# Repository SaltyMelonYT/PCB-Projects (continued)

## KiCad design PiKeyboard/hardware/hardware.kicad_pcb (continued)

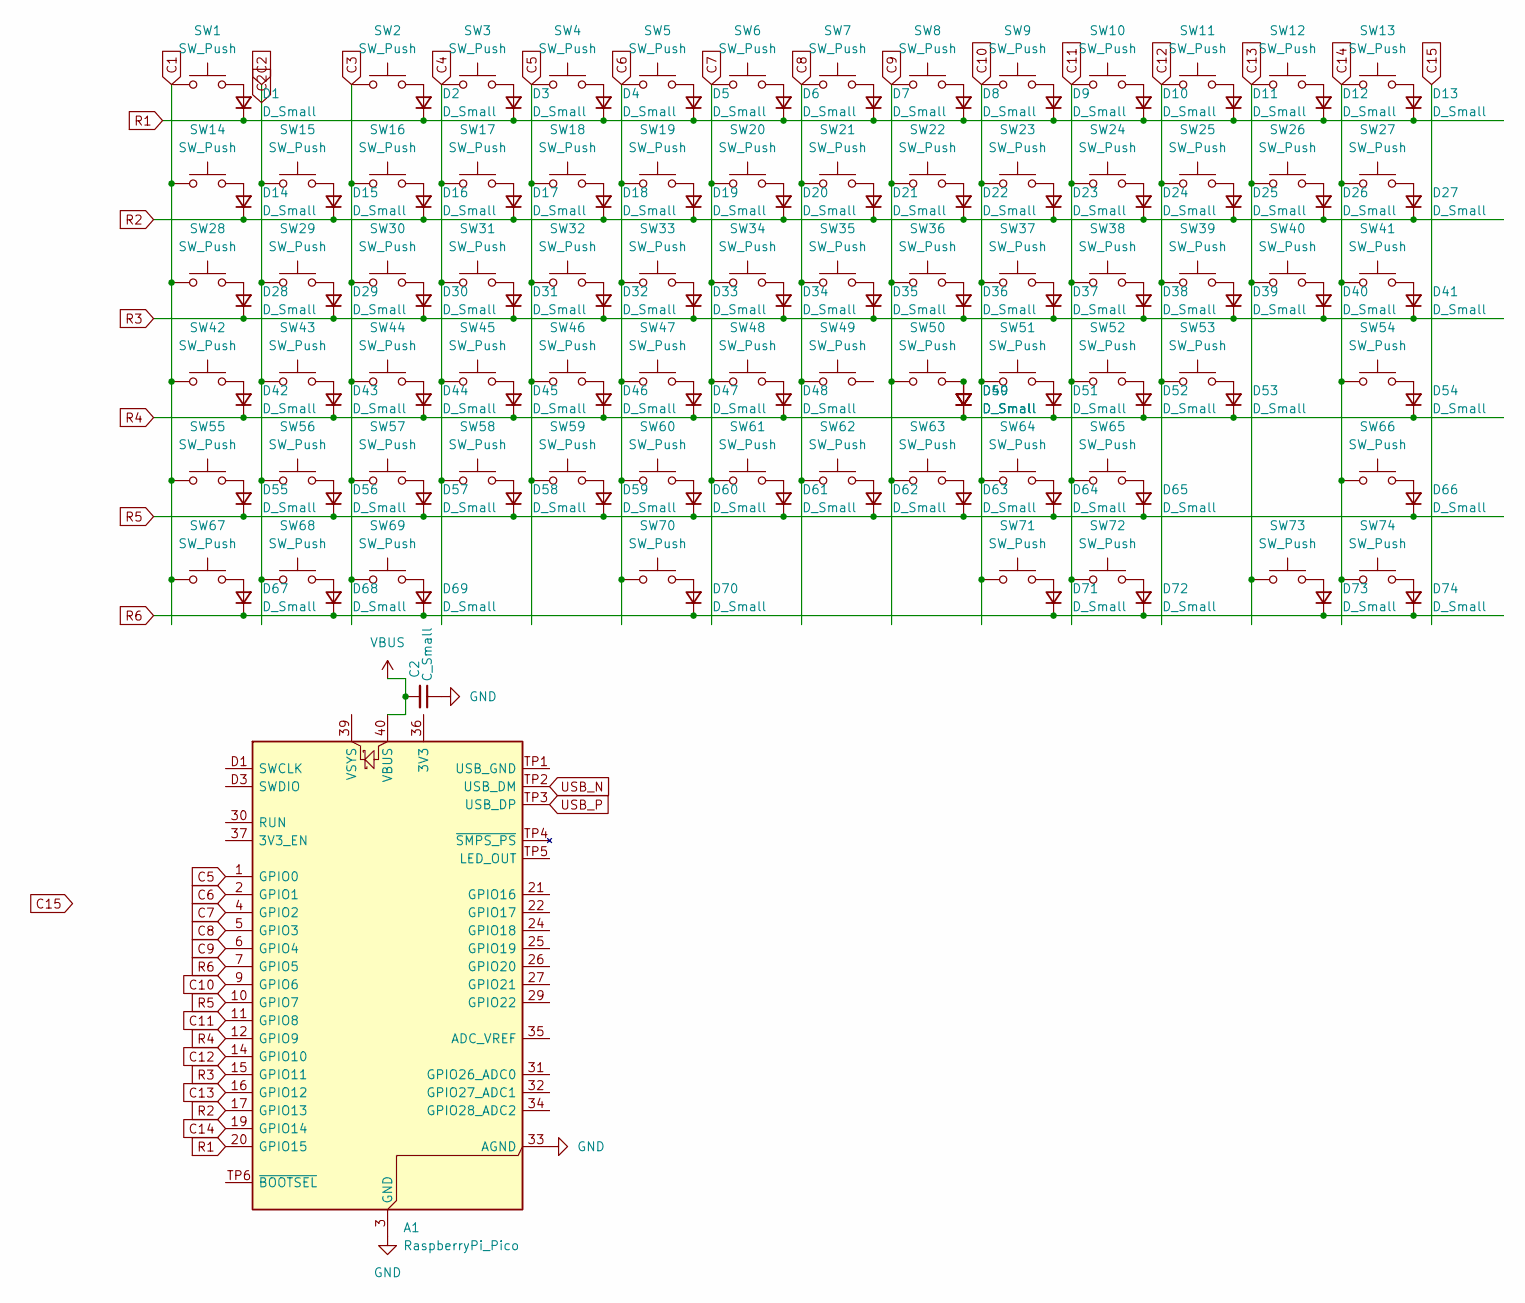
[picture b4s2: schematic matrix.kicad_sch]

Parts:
A1: RaspberryPi_Pico; RaspberryPi_Pico_SMD
C2: C_Small; C_0805_2012Metric_Pad1.18x1.45mm_HandSolder
D1, D2, D3, D4, D5, D6, D7, D8, D9, D10, D11, D12, D13, D14, D15, D16, D17, D18, D19, D20, D21, D22, D23, D24, D25, D26, D27, D28, D29, D30, D31, D32, D33, D34, D35, D36, D37, D38, D39, D40, D41, D42, D43, D44, D45, D46, D47, D48, D49, D50, D51, D52, D53, D54, D55, D56, D57, D58, D59, D60, D61, D62, D63, D64, D65, D66, D67, D68, D69, D70, D71, D72, D73, D74: D_Small; D_0402_1005Metric_Pad0.77x0.64mm_HandSolder
SW1, SW2, SW3, SW4, SW5, SW6, SW7, SW8, SW9, SW10, SW11, SW12, SW13, SW14, SW15, SW16, SW17, SW18, SW19, SW20, SW21, SW22, SW23, SW24, SW25, SW26, SW29, SW30, SW31, SW32, SW33, SW34, SW35, SW36, SW37, SW38, SW39, SW40, SW43, SW44, SW45, SW46, SW47, SW48, SW49, SW50, SW51, SW52, SW53, SW56, SW57, SW58, SW59, SW60, SW61, SW62, SW63, SW64, SW65: SW_Push; SW_Cherry_MX_PCB_1.00u
SW27, SW55: SW_Push; SW_Cherry_MX_PCB_2.00u
SW28, SW41: SW_Push; SW_Cherry_MX_PCB_1.50u
SW42: SW_Push; SW_Cherry_MX_PCB_1.75u
SW54: SW_Push; SW_Cherry_MX_PCB_2.25u
SW66: SW_Push; SW_Cherry_MX_PCB_3.00u
SW67, SW68, SW69, SW71, SW72, SW73, SW74: SW_Push; SW_Cherry_MX_PCB_1.25u
SW70: SW_Push; SW_Cherry_MX_PCB_6.25u

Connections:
C1: SW1.1, SW14.1, SW28.1, SW42.1, SW55.1, SW67.1
C2: SW15.1, SW29.1, SW43.1, SW56.1, SW68.1
C3: SW2.1, SW16.1, SW30.1, SW44.1, SW57.1, SW69.1
C4: SW3.1, SW17.1, SW31.1, SW45.1, SW58.1
C5: A1.1 (GPIO0), SW4.1, SW18.1, SW32.1, SW46.1, SW59.1
C6: A1.2 (GPIO1), SW5.1, SW19.1, SW33.1, SW47.1, SW60.1, SW70.1
C7: A1.4 (GPIO2), SW6.1, SW20.1, SW34.1, SW48.1, SW61.1
C8: A1.5 (GPIO3), SW7.1, SW21.1, SW35.1, SW49.1, SW62.1
C9: A1.6 (GPIO4), SW8.1, SW22.1, SW36.1, SW50.1, SW63.1
C10: A1.9 (GPIO6), SW9.1, SW23.1, SW37.1, SW51.1, SW64.1, SW71.1
C11: A1.11 (GPIO8), SW10.1, SW24.1, SW38.1, SW52.1, SW65.1, SW72.1
C12: A1.14 (GPIO10), SW11.1, SW25.1, SW39.1, SW53.1
C13: A1.16 (GPIO12), SW12.1, SW26.1, SW40.1, SW73.1
C14: A1.19 (GPIO14), SW13.1, SW27.1, SW41.1, SW54.1, SW66.1, SW74.1
GND: A1.3 (GND), A1.8 (GND), A1.13 (GND), A1.18 (GND), A1.23 (GND), A1.28 (GND), A1.33 (AGND), A1.38 (GND), A1.D2 (GND), C2.1; also elsewhere on the board
unnamed: D1.2 (A), SW1.2
unnamed: D2.2 (A), SW2.2
unnamed: D3.2 (A), SW3.2
unnamed: D4.2 (A), SW4.2
unnamed: D5.2 (A), SW5.2
unnamed: D6.2 (A), SW6.2
unnamed: D7.2 (A), SW7.2
unnamed: D8.2 (A), SW8.2
unnamed: D9.2 (A), SW9.2
unnamed: D10.2 (A), SW10.2
unnamed: D11.2 (A), SW11.2
unnamed: D12.2 (A), SW12.2
unnamed: D13.2 (A), SW13.2
unnamed: D14.2 (A), SW14.2
unnamed: D15.2 (A), SW15.2
unnamed: D16.2 (A), SW16.2
unnamed: D17.2 (A), SW17.2
unnamed: D18.2 (A), SW18.2
unnamed: D19.2 (A), SW19.2
unnamed: D20.2 (A), SW20.2
unnamed: D21.2 (A), SW21.2
unnamed: D22.2 (A), SW22.2
unnamed: D23.2 (A), SW23.2
unnamed: D24.2 (A), SW24.2
unnamed: D25.2 (A), SW25.2
unnamed: D26.2 (A), SW26.2
unnamed: D27.2 (A), SW27.2
unnamed: D28.2 (A), SW28.2
unnamed: D29.2 (A), SW29.2
unnamed: D30.2 (A), SW30.2
unnamed: D31.2 (A), SW31.2
unnamed: D32.2 (A), SW32.2
unnamed: D33.2 (A), SW33.2
unnamed: D34.2 (A), SW34.2
unnamed: D35.2 (A), SW35.2
unnamed: D36.2 (A), SW36.2
unnamed: D37.2 (A), SW37.2
unnamed: D38.2 (A), SW38.2
unnamed: D39.2 (A), SW39.2
unnamed: D40.2 (A), SW40.2
unnamed: D41.2 (A), SW41.2
unnamed: D42.2 (A), SW42.2
unnamed: D43.2 (A), SW43.2
unnamed: D44.2 (A), SW44.2
unnamed: D45.2 (A), SW45.2
unnamed: D46.2 (A), SW46.2
unnamed: D47.2 (A), SW47.2
unnamed: D48.2 (A), SW48.2
unnamed: D49.2 (A), D50.2 (A), SW50.2
unnamed: D51.2 (A), SW51.2
unnamed: D52.2 (A), SW52.2
unnamed: D53.2 (A), SW53.2
unnamed: D54.2 (A), SW54.2
unnamed: D55.2 (A), SW55.2
unnamed: D56.2 (A), SW56.2
unnamed: D57.2 (A), SW57.2
unnamed: D58.2 (A), SW58.2
unnamed: D59.2 (A), SW59.2
unnamed: D60.2 (A), SW60.2
unnamed: D61.2 (A), SW61.2
unnamed: D62.2 (A), SW62.2
unnamed: D63.2 (A), SW63.2
unnamed: D64.2 (A), SW64.2
unnamed: D65.2 (A), SW65.2
unnamed: D66.2 (A), SW66.2
unnamed: D67.2 (A), SW67.2
unnamed: D68.2 (A), SW68.2
unnamed: D69.2 (A), SW69.2
unnamed: D70.2 (A), SW70.2
unnamed: D71.2 (A), SW71.2
unnamed: D72.2 (A), SW72.2
unnamed: D73.2 (A), SW73.2
unnamed: D74.2 (A), SW74.2
R1: A1.20 (GPIO15), D1.1 (K), D2.1 (K), D3.1 (K), D4.1 (K), D5.1 (K), D6.1 (K), D7.1 (K), D8.1 (K), D9.1 (K), D10.1 (K), D11.1 (K), D12.1 (K), D13.1 (K)
R2: A1.17 (GPIO13), D14.1 (K), D15.1 (K), D16.1 (K), D17.1 (K), D18.1 (K), D19.1 (K), D20.1 (K), D21.1 (K), D22.1 (K), D23.1 (K), D24.1 (K), D25.1 (K), D26.1 (K), D27.1 (K)
R3: A1.15 (GPIO11), D28.1 (K), D29.1 (K), D30.1 (K), D31.1 (K), D32.1 (K), D33.1 (K), D34.1 (K), D35.1 (K), D36.1 (K), D37.1 (K), D38.1 (K), D39.1 (K), D40.1 (K), D41.1 (K)
R4: A1.12 (GPIO9), D42.1 (K), D43.1 (K), D44.1 (K), D45.1 (K), D46.1 (K), D47.1 (K), D48.1 (K), D49.1 (K), D50.1 (K), D51.1 (K), D52.1 (K), D53.1 (K), D54.1 (K)
R5: A1.10 (GPIO7), D55.1 (K), D56.1 (K), D57.1 (K), D58.1 (K), D59.1 (K), D60.1 (K), D61.1 (K), D62.1 (K), D63.1 (K), D64.1 (K), D65.1 (K), D66.1 (K)
R6: A1.7 (GPIO5), D67.1 (K), D68.1 (K), D69.1 (K), D70.1 (K), D71.1 (K), D72.1 (K), D73.1 (K), D74.1 (K)
USB_N: A1.TP2 (USB_DM); also elsewhere on the board
USB_P: A1.TP3 (USB_DP); also elsewhere on the board
VBUS: A1.40 (VBUS), C2.2; also elsewhere on the board

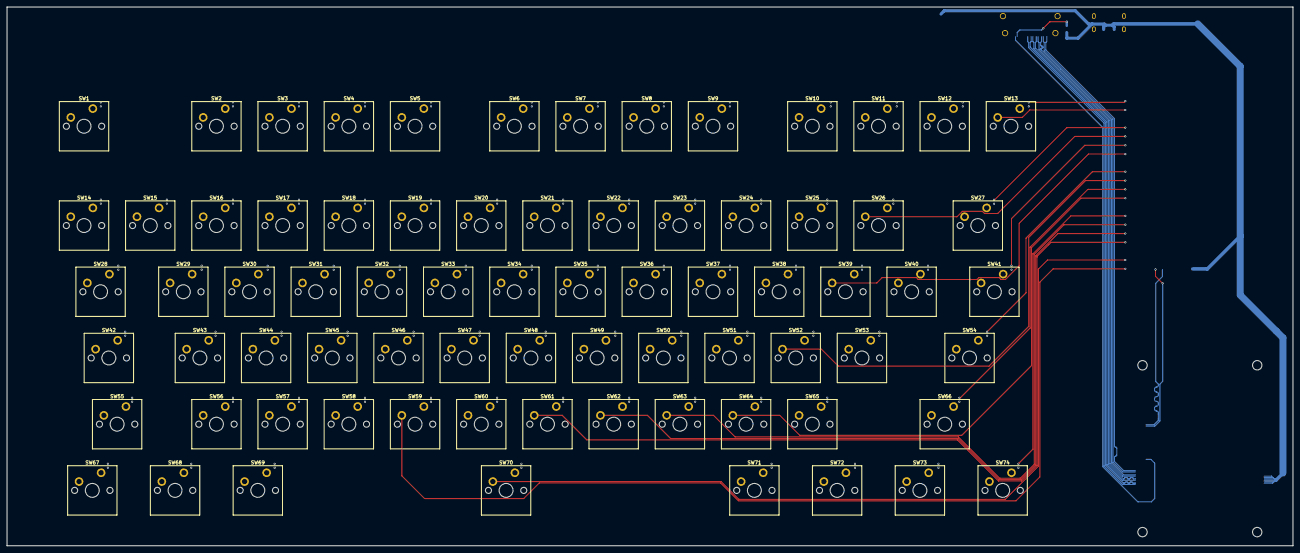
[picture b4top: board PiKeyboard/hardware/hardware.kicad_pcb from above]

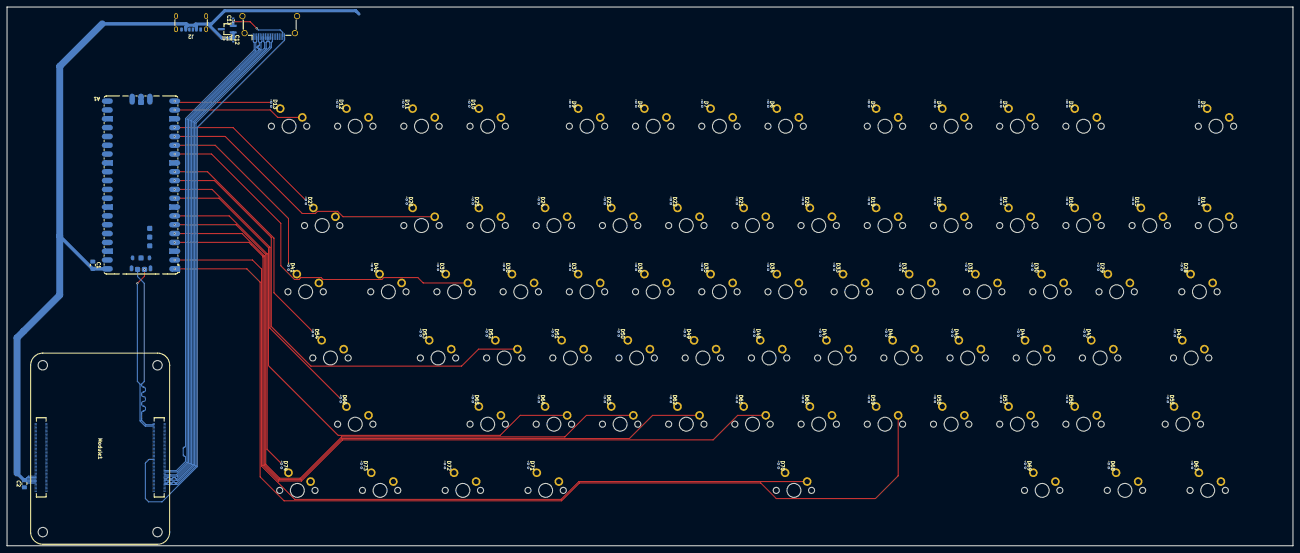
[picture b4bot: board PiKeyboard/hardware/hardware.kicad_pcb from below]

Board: 4 copper layers, 370.0 x 155.0 mm, 157 parts (83 on the bottom side), 109 nets.

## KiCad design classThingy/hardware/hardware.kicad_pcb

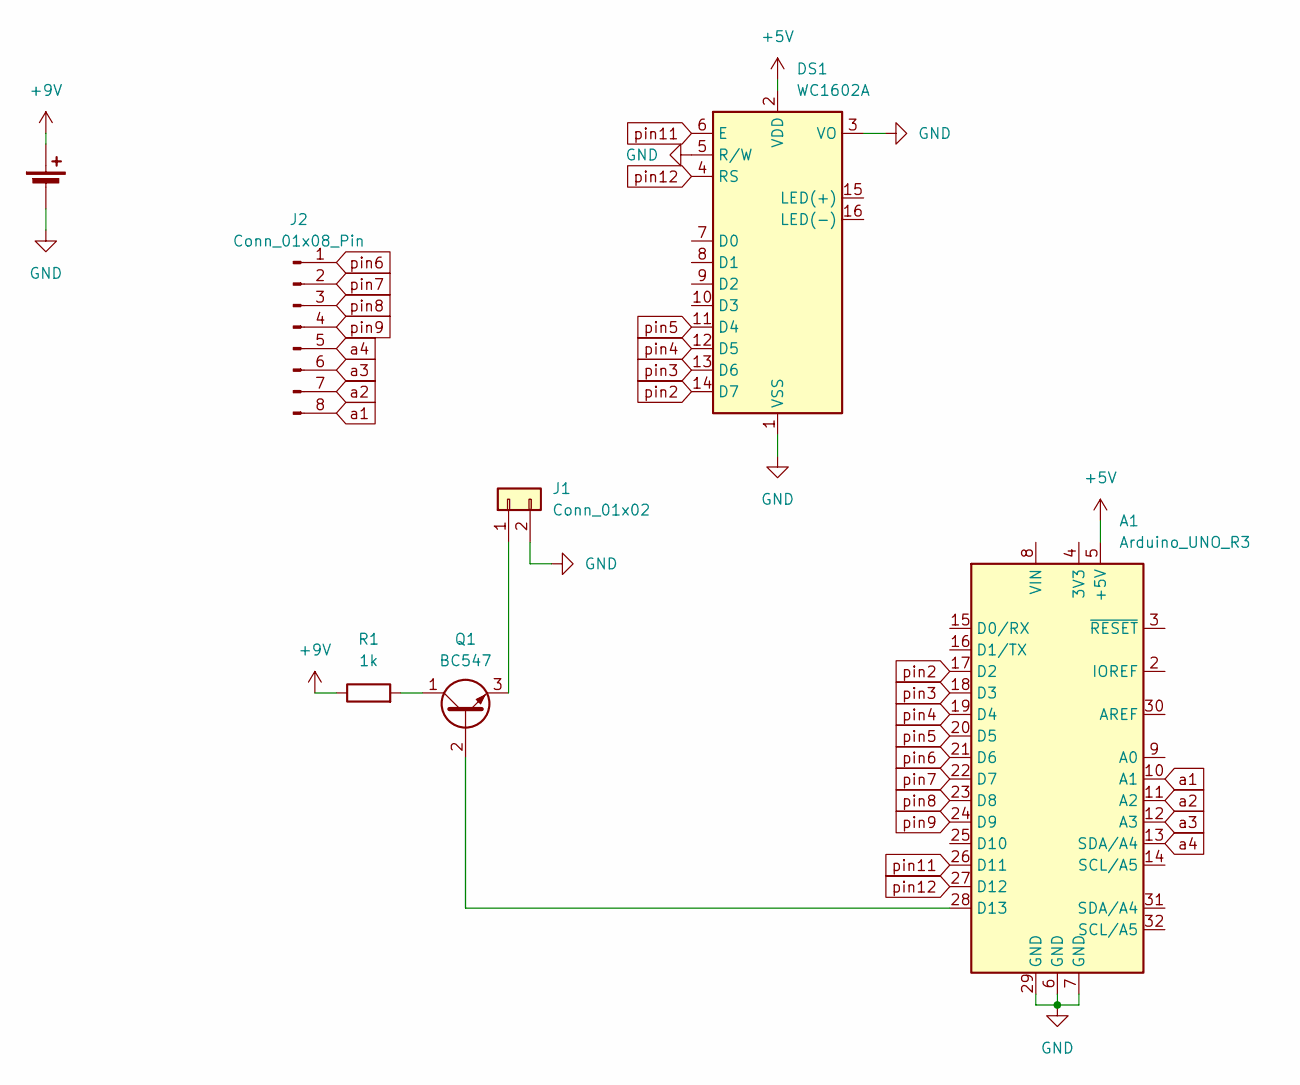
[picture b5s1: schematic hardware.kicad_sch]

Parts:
A1: Arduino_UNO_R3
BT1: +9V; BatteryHolder_Eagle_12BH611-GR
DS1: WC1602A
J1: Conn_01x02; PinHeader_1x02_P1.27mm_Vertical
J2: Conn_01x08_Pin; PinHeader_1x08_P1.27mm_Vertical
Q1: BC547; TO-92_Inline
R1: 1k; R_2512_6332Metric_Pad1.40x3.35mm_HandSolder

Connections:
+5V: A1.5 (+5V), DS1.2 (VDD)
+9V: BT1.1 (+), R1.1
GND: A1.6 (GND), A1.7 (GND), A1.29 (GND), BT1.2 (-), DS1.1 (VSS), DS1.3 (VO), DS1.5 (R/W), J1.2
unnamed: A1.28 (D13), Q1.2 (B)
unnamed: J1.1, Q1.3 (E)
unnamed: Q1.1 (C), R1.2
a1: A1.10 (A1), J2.8
a2: A1.11 (A2), J2.7
a3: A1.12 (A3), J2.6
a4: A1.13 (SDA/A4), J2.5
pin2: A1.17 (D2), DS1.14 (D7)
pin3: A1.18 (D3), DS1.13 (D6)
pin4: A1.19 (D4), DS1.12 (D5)
pin5: A1.20 (D5), DS1.11 (D4)
pin6: A1.21 (D6), J2.1
pin7: A1.22 (D7), J2.2
pin8: A1.23 (D8), J2.3
pin9: A1.24 (D9), J2.4
pin11: A1.26 (D11), DS1.6 (E)
pin12: A1.27 (D12), DS1.4 (RS)

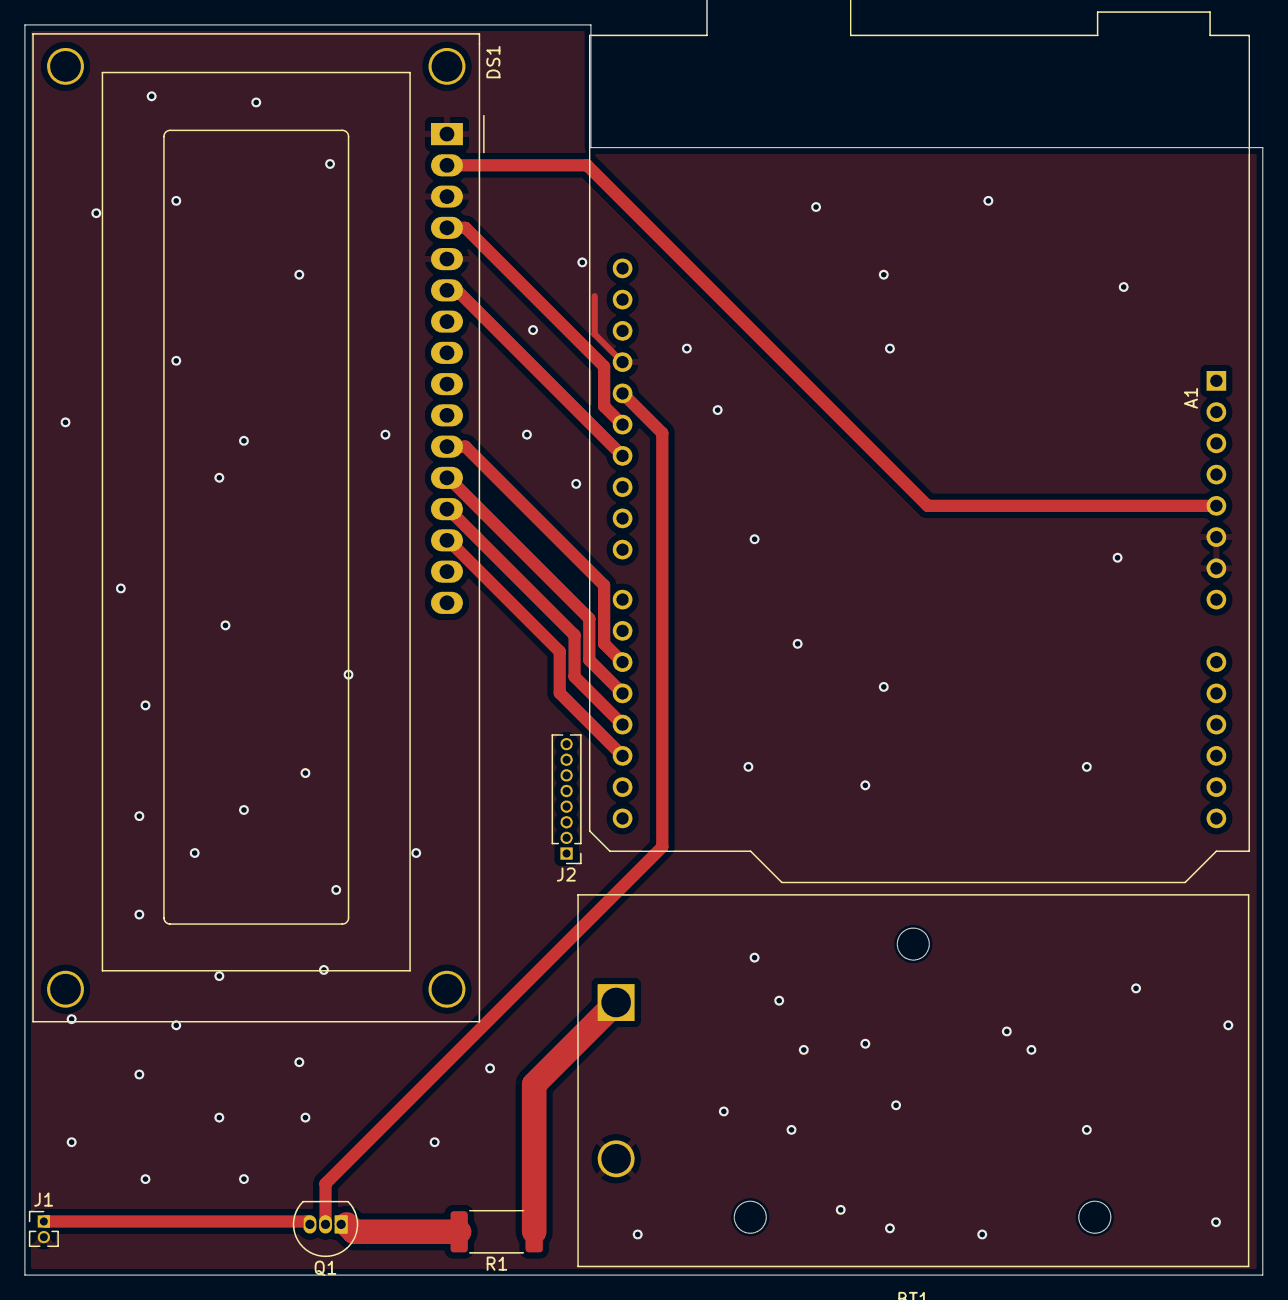
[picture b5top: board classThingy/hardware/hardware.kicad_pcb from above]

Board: 4 copper layers, 100.6 x 101.6 mm, 7 parts (0 on the bottom side), 20 nets.

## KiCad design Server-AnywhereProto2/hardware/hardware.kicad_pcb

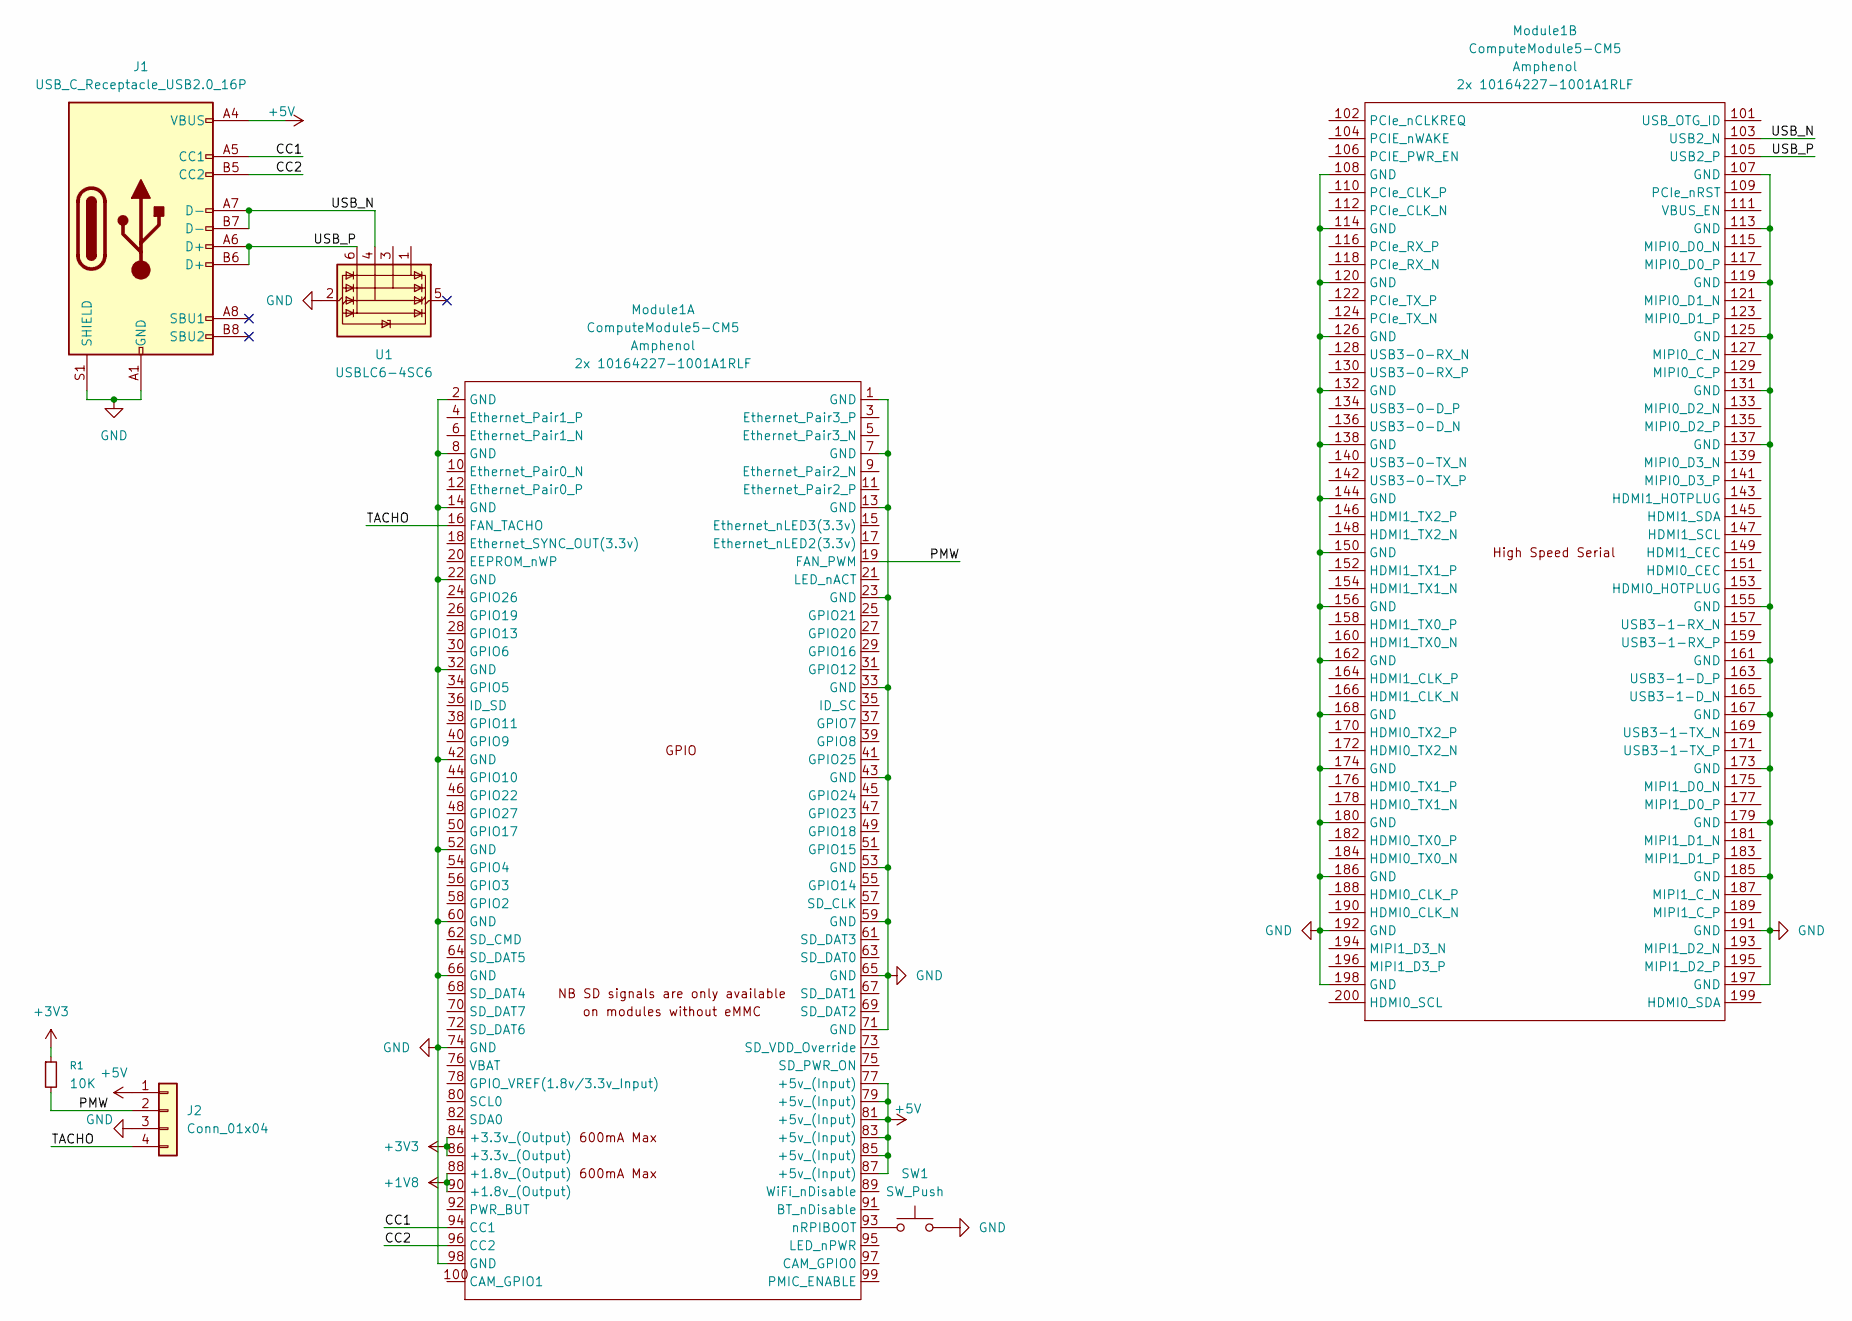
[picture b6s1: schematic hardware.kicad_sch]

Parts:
J1: USB_C_Receptacle_USB2.0_16P; USB_C_Receptacle_GCT_USB4105-xx-A_16P_TopMnt_Horizontal
J2: Conn_01x04; JST_SH_BM04B-SRSS-TB_1x04-1MP_P1.00mm_Vertical
Module1: ComputeModule5-CM5; Raspberry-Pi-5-Compute-Module
R1: 10K; R_2512_6332Metric_Pad1.40x3.35mm_HandSolder
SW1: SW_Push; SW_PUSH_6mm
U1: USBLC6-4SC6; SOT-23-6

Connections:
+1V8: Module1.88 (+1.8v_(Output)), Module1.90 (+1.8v_(Output))
+3V3: Module1.84 (+3.3v_(Output)), Module1.86 (+3.3v_(Output)), R1.1
+5V: J1.A4 (VBUS), J1.A9 (VBUS), J1.B4 (VBUS), J1.B9 (VBUS), J2.1, Module1.77 (+5v_(Input)), Module1.79 (+5v_(Input)), Module1.81 (+5v_(Input)), Module1.83 (+5v_(Input)), Module1.85 (+5v_(Input)), Module1.87 (+5v_(Input))
/CC1: J1.A5 (CC1), Module1.94 (CC1)
/CC2: J1.B5 (CC2), Module1.96 (CC2)
/PMW: J2.2, Module1.19 (FAN_PWM), R1.2
/TACHO: J2.4, Module1.16 (FAN_TACHO)
/USB_N: J1.A7 (D-), J1.B7 (D-), Module1.103 (USB2_N), U1.4 (I/O3)
/USB_P: J1.A6 (D+), J1.B6 (D+), Module1.105 (USB2_P), U1.6 (I/O4)
GND: J1.A1 (GND), J1.A12 (GND), J1.B1 (GND), J1.B12 (GND), J1.S1 (SHIELD), J2.3, Module1.1 (GND), Module1.2 (GND), Module1.7 (GND), Module1.8 (GND), Module1.13 (GND), Module1.14 (GND), Module1.22 (GND), Module1.23 (GND), Module1.32 (GND), Module1.33 (GND), Module1.42 (GND), Module1.43 (GND), Module1.52 (GND), Module1.53 (GND), Module1.59 (GND), Module1.60 (GND), Module1.65 (GND), Module1.66 (GND), Module1.71 (GND), Module1.74 (GND), Module1.98 (GND), Module1.107 (GND), Module1.108 (GND), Module1.113 (GND), Module1.114 (GND), Module1.119 (GND), Module1.120 (GND), Module1.125 (GND), Module1.126 (GND), Module1.131 (GND), Module1.132 (GND), Module1.137 (GND), Module1.138 (GND), Module1.144 (GND), Module1.150 (GND), Module1.155 (GND), Module1.156 (GND), Module1.161 (GND), Module1.162 (GND), Module1.167 (GND), Module1.168 (GND), Module1.173 (GND), Module1.174 (GND), Module1.179 (GND), Module1.180 (GND), Module1.185 (GND), Module1.186 (GND), Module1.191 (GND), Module1.192 (GND), Module1.197 (GND), Module1.198 (GND), SW1.2, U1.2 (GND)
unnamed: Module1.93 (nRPIBOOT), SW1.1

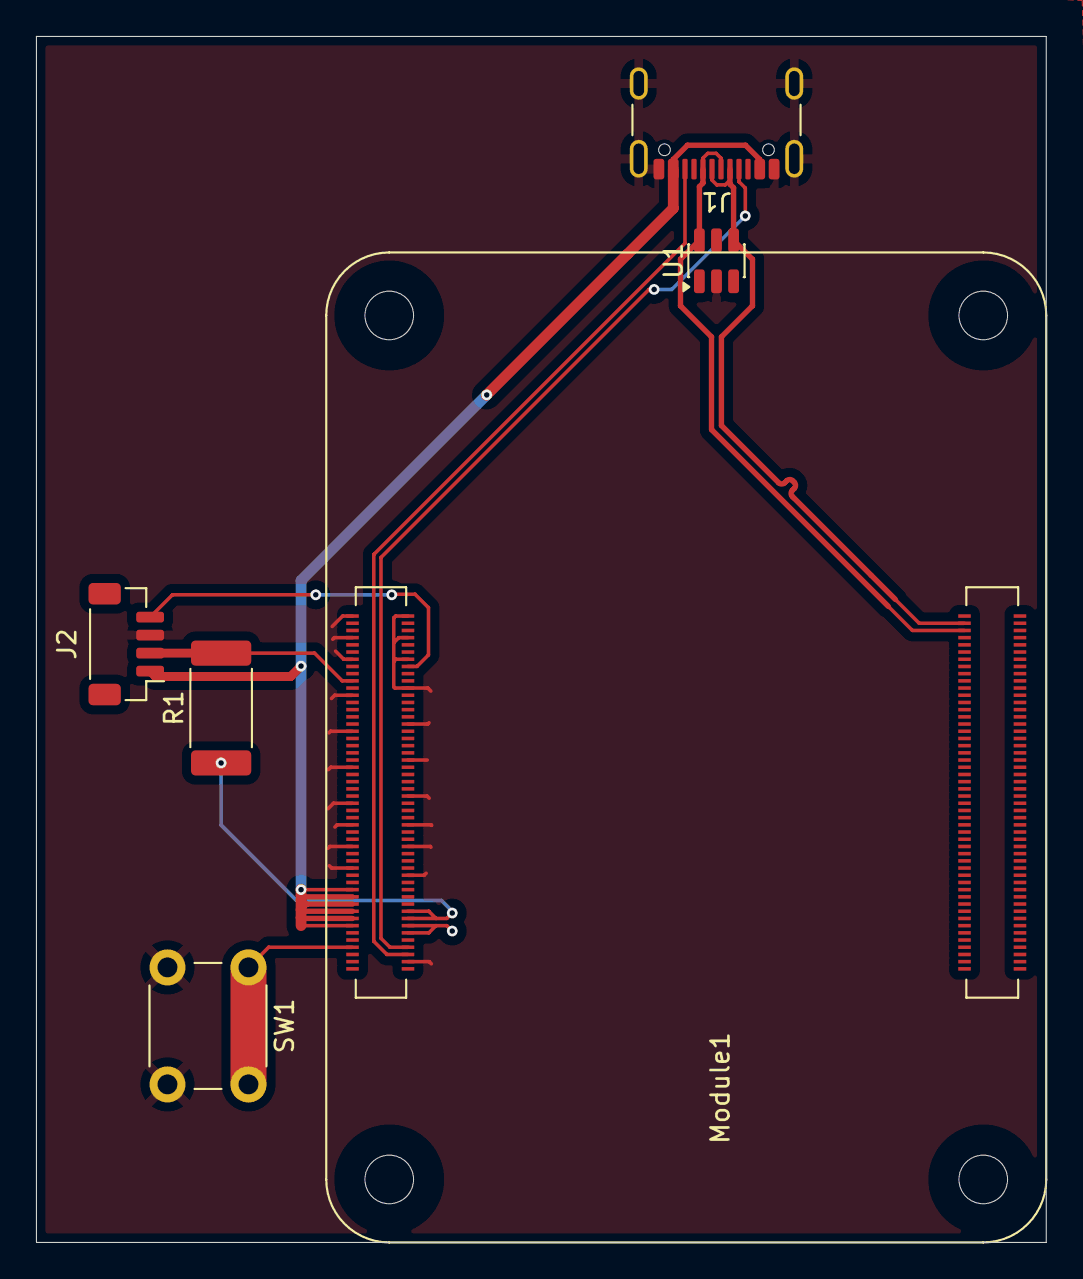
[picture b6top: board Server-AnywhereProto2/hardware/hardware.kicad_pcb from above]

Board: 2 copper layers, 56.1 x 67.0 mm, 6 parts (0 on the bottom side), 11 nets.

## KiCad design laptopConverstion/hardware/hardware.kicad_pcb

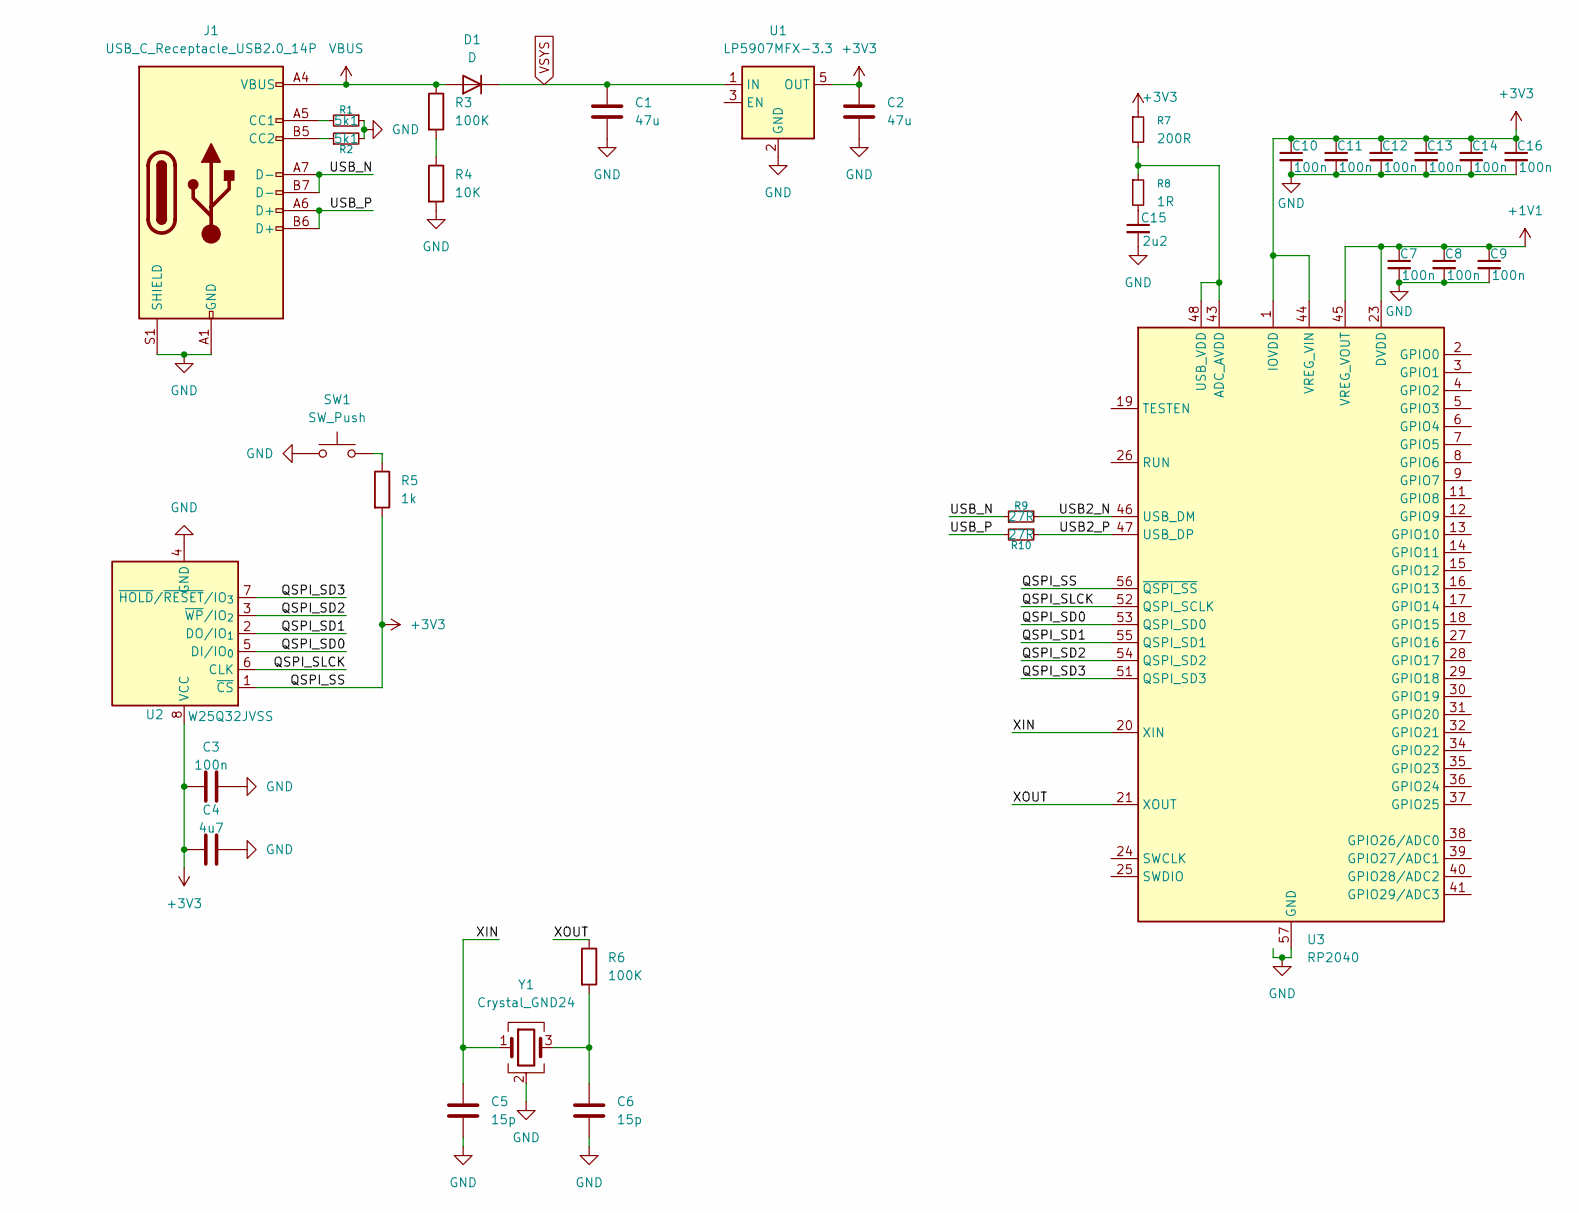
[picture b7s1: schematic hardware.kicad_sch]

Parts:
C1, C2: 47u; C_1812_4532Metric_Pad1.57x3.40mm_HandSolder
C3: 100n; C_1812_4532Metric_Pad1.57x3.40mm_HandSolder
C4: 4u7; C_1812_4532Metric_Pad1.57x3.40mm_HandSolder
C5, C6: 15p; C_1812_4532Metric_Pad1.57x3.40mm_HandSolder
C7, C8, C9, C10, C11, C12, C13, C14, C16: 100n; C_1206_3216Metric_Pad1.33x1.80mm_HandSolder
C15: 2u2; C_1206_3216Metric_Pad1.33x1.80mm_HandSolder
D1: D; D_1210_3225Metric_Pad1.42x2.65mm_HandSolder
J1: USB_C_Receptacle_USB2.0_14P; USB_C_Receptacle_GCT_USB4105-xx-A_16P_TopMnt_Horizontal
R1, R2: 5k1; R_1210_3225Metric_Pad1.30x2.65mm_HandSolder
R3: 100K; R_1210_3225Metric_Pad1.30x2.65mm_HandSolder
R4: 10K; R_1210_3225Metric_Pad1.30x2.65mm_HandSolder
R5: 1k; R_1210_3225Metric_Pad1.30x2.65mm_HandSolder
R6: 100K; R_0805_2012Metric_Pad1.20x1.40mm_HandSolder
R7: 200R; R_0805_2012Metric_Pad1.20x1.40mm_HandSolder
R8: 1R; R_0805_2012Metric_Pad1.20x1.40mm_HandSolder
R9, R10: 27R; R_0805_2012Metric_Pad1.20x1.40mm_HandSolder
SW1: SW_Push; SW_PUSH_6mm
U1: LP5907MFX-3.3; SOT-23-5
U2: W25Q32JVSS; SOIC-8_5.3x5.3mm_P1.27mm
U3: RP2040; QFN-56-1EP_7x7mm_P0.4mm_EP3.2x3.2mm
Y1: Crystal_GND24; Crystal_SMD_0603-4Pin_6.0x3.5mm_HandSoldering

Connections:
+1V1: C7.1, C8.1, C9.1, U3.23 (DVDD), U3.45 (VREG_VOUT), U3.50 (DVDD)
+3V3: C2.1, C3.1, C4.1, C10.1, C11.1, C12.1, C13.1, C14.1, C16.1, R5.2, R7.1, U1.5 (OUT), U2.1 (~CS), U2.8 (VCC), U3.1 (IOVDD), U3.10 (IOVDD), U3.22 (IOVDD), U3.33 (IOVDD), U3.42 (IOVDD), U3.44 (VREG_VIN), U3.49 (IOVDD), U3.56 (~QSPI_SS)
/QSPI_SD0: U2.5 (DI/IO_{0}), U3.53 (QSPI_SD0)
/QSPI_SD1: U2.2 (DO/IO_{1}), U3.55 (QSPI_SD1)
/QSPI_SD2: U2.3 (~WP/IO_{2}), U3.54 (QSPI_SD2)
/QSPI_SD3: U2.7 (~HOLD/~RESET/IO_{3}), U3.51 (QSPI_SD3)
/QSPI_SLCK: U2.6 (CLK), U3.52 (QSPI_SCLK)
/USB2_N: R9.2, U3.46 (USB_DM)
/USB2_P: R10.1, U3.47 (USB_DP)
/USB_N: J1.A7 (D-), J1.B7 (D-), R9.1
/USB_P: J1.A6 (D+), J1.B6 (D+), R10.2
/XIN: C5.1, U3.20 (XIN), Y1.1
/XOUT: R6.1, U3.21 (XOUT)
GND: C1.2, C2.2, C3.2, C4.2, C5.2, C6.2, C7.2, C8.2, C9.2, C10.2, C11.2, C12.2, C13.2, C14.2, C15.2, C16.2, J1.A1 (GND), J1.A12 (GND), J1.B1 (GND), J1.B12 (GND), J1.S1 (SHIELD), R1.1, R2.2, R4.2, SW1.1, U1.2 (GND), U2.4 (GND), U3.57 (GND), Y1.2 (G), Y1.4 (G)
unnamed: C6.1, R6.2, Y1.3
unnamed: C15.1, R8.2
unnamed: J1.A5 (CC1), R1.2
unnamed: J1.B5 (CC2), R2.1
unnamed: R3.2, R4.1
unnamed: R5.1, SW1.2
unnamed: R7.2, R8.1, U3.43 (ADC_AVDD), U3.48 (USB_VDD)
VBUS: D1.2 (A), J1.A4 (VBUS), J1.A9 (VBUS), J1.B4 (VBUS), J1.B9 (VBUS), R3.1
VSYS: C1.1, D1.1 (K), U1.1 (IN)

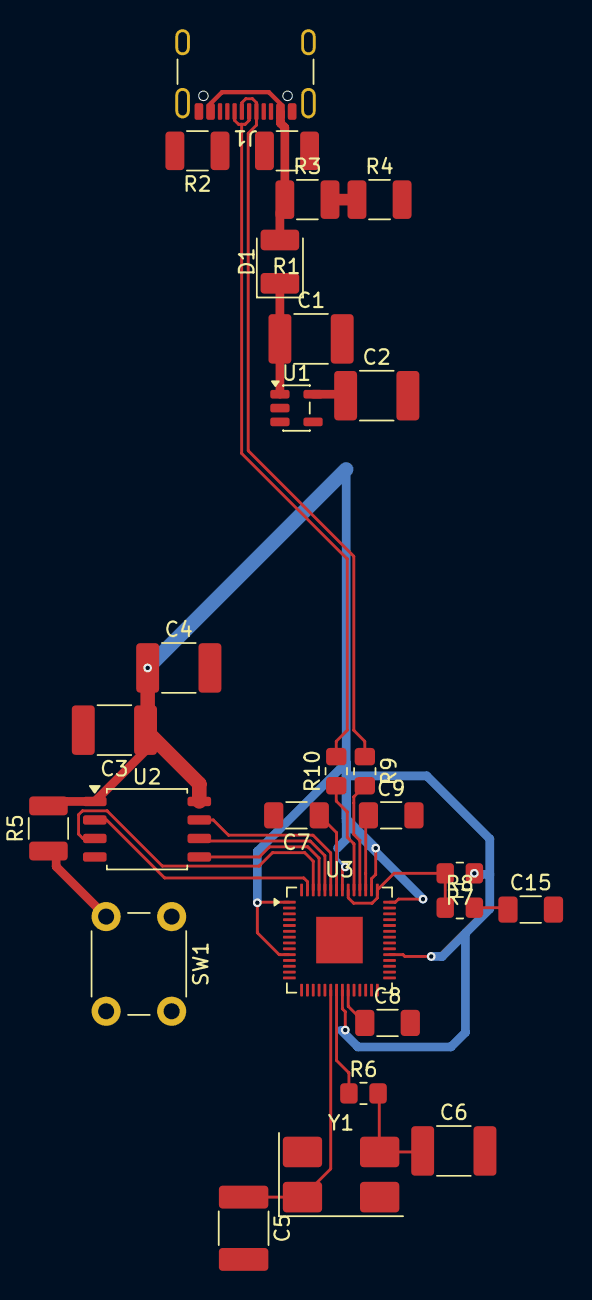
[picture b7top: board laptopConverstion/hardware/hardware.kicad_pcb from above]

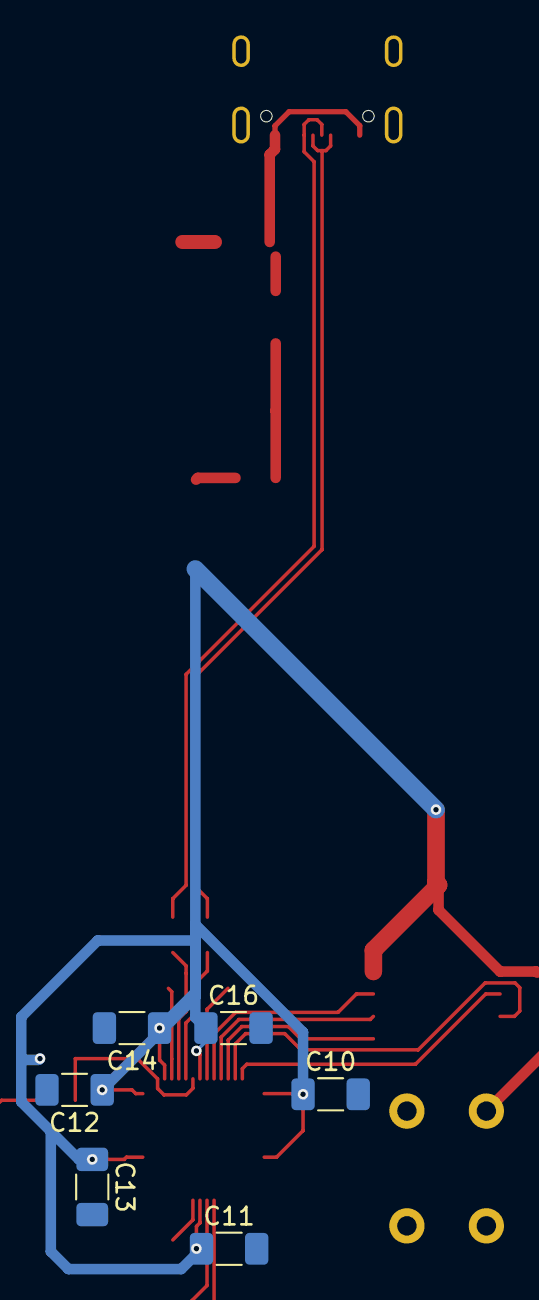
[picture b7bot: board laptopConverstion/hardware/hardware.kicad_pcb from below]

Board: 2 copper layers, 33 parts (6 on the bottom side), 23 nets.
